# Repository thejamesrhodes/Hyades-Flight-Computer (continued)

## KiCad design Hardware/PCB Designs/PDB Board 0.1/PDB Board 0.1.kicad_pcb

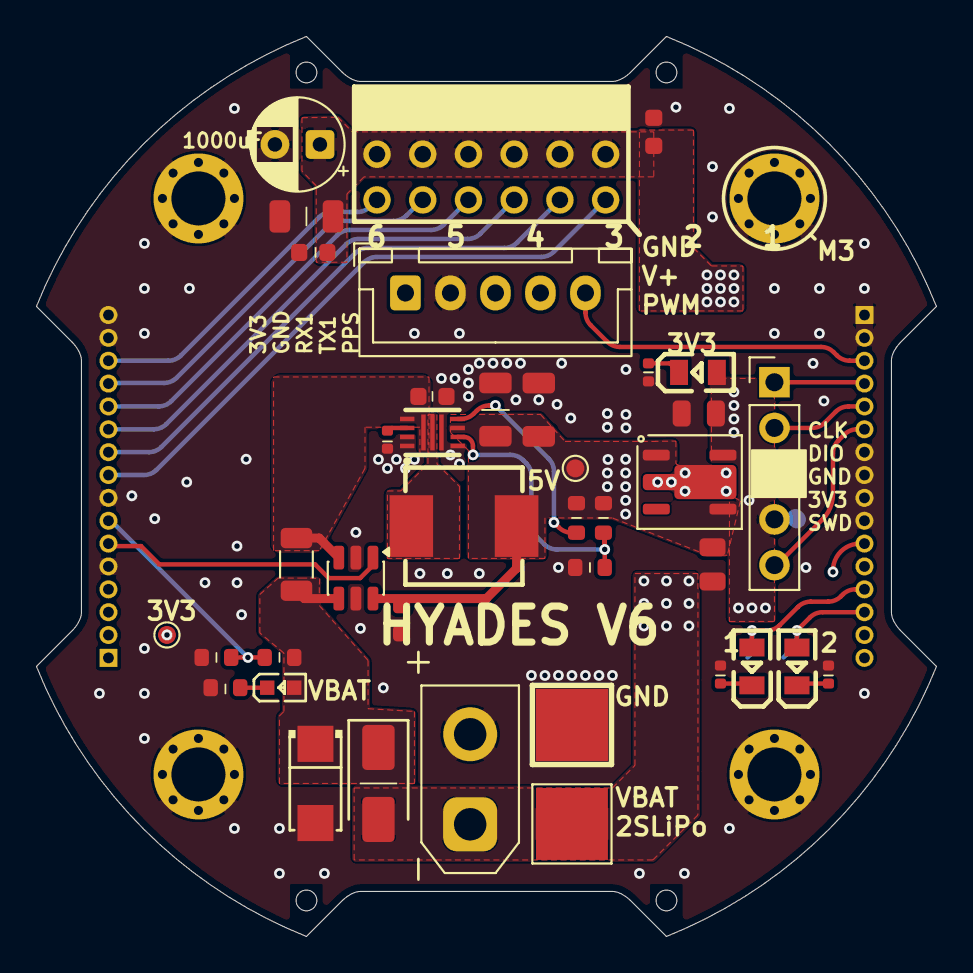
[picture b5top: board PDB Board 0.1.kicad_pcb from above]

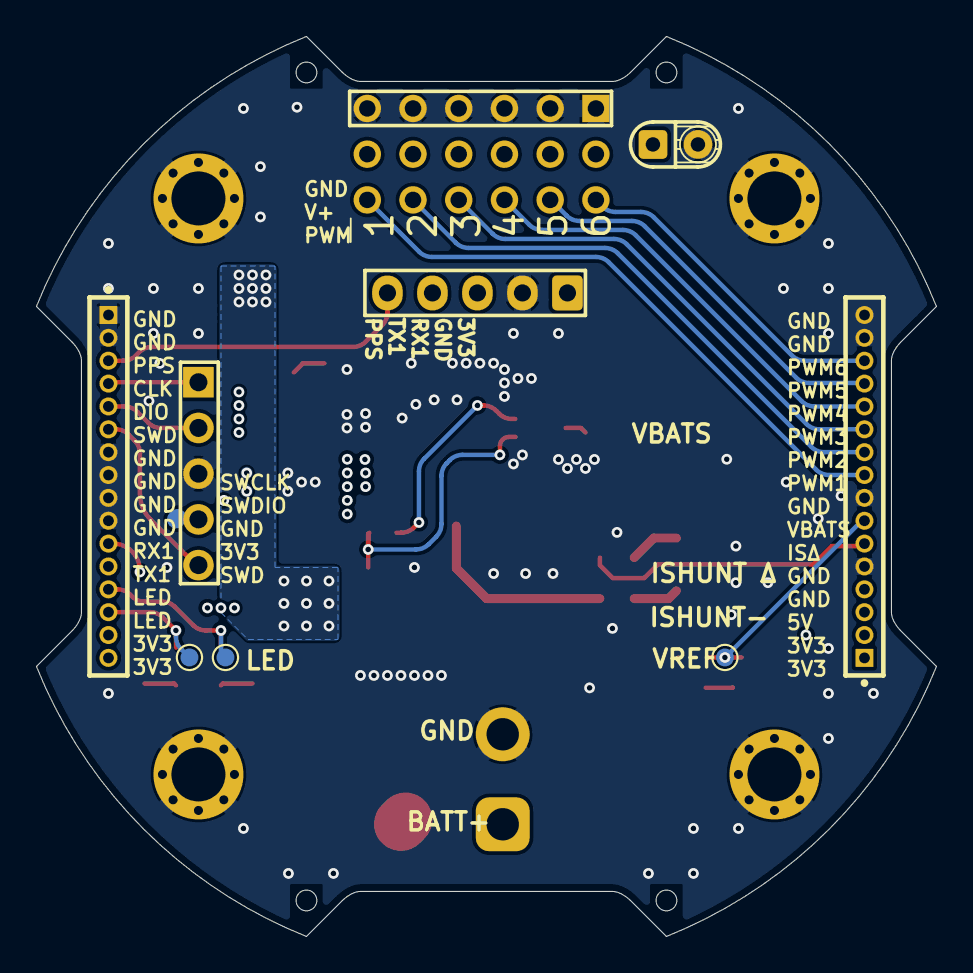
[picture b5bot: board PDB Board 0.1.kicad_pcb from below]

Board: 4 copper layers, 50.0 x 50.0 mm, 52 parts (5 on the bottom side), 30 nets.

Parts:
BT1: Battery; AMASS_XT30UPB-M_1x02_P5.0mm_Vertical
C1, C4, C5: 100nF; C_0603
C6, C7: 10uF; C_1206
C9: 1000uF_16V; CP_Radial_D5.0mm_P2.50mm
C10: 100uF; C_1206
C11, C12: 10uF; C_0805
C18: 10uF; C_0603
C19: 2.2nF; C_0402
D1: SMAJ15A_C908769
D2: SS34; D_SMA
H1, H2, H3, H4: Hole, 3mm
H5, H6, H7, H8: Hole_Tooling_JLCPCB
H9: HX_PZ2_54-3X6P_ZZ
J7: Conn_01x05; JST_XH_B5B-XH-A_1x05_P2.50mm_Vertical
J8: Conn_01x05; PinHeader_1x05_P2.54mm_Vertical
LED1: KT-0603R
LED2, LED4: 17-21SUYC_TR8
LED3: 0805G_Green
R1: 100kΩ; R_0603
R2: 33kΩ; R_0603
R3: 10m_1206_250mW; R_1206_3216Metric
R4: 180kΩ; R_0603
R5: 470Ω; R_0603
R6, R7, R8: 220Ω; R_0402
R15: 62kΩ; R_0603
R16: 10kΩ; R_0603
TP1: BATT-; TestPoint_Pad_4.0x4.0mm
TP2: BATT+; TestPoint_Pad_4.0x4.0mm
TP3, TP4, TP13, TP16, TP17: TestPoint; TestPoint_Pad_D1.0mm
U1: TPS62135RGXR
U2: IHLP2525CZER1R0M01
U3: INA181A1IDBVT; SOT-23-6
U4: AP2115R5A-3.3TRG1; Diodes_SOT-89-5
U6, U7: X1311FV-16-C43D24

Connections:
+3V3: C12.1, J7.1, J8.4, LED2.1 (+), TP4.1 (1_1), U4.5 (OUT), U6.1, U6.2, U7.15, U7.16
+5V: C5.1, C6.1, C7.1, C11.1, R1.2, R15.1, TP3.1 (1_1), U1.6 (VOS), U2.2, U3.6 (V+), U4.1 (EN), U4.4 (IN), U6.3, U6.4
+BATT: BT1.1 (+), C1.1, C4.1, C9.1, C10.1, D2.2, H9.7, H9.8, H9.9, H9.10, H9.11, H9.12, TP2.1 (1_1)
/VDD_BUCK: C18.1, R3.2, U1.1 (VIN), U1.8 (EN), U3.3 (+)
GND: BT1.2 (-), C1.2, C4.2, C5.2, C6.2, C7.2, C9.2, C10.2, C11.2, C12.2, C18.2, C19.2, D1.2, H1.1, H2.1, H3.1, H4.1, H9.1, H9.2, H9.3, H9.4, H9.5, H9.6, J7.2, J8.3, R2.2, R5.1, R6.2, R7.2, R8.2, R16.2, TP1.1 (1_1), U1.3 (GND), U1.4 (FB2), U1.10 (MODE), U1.11 (VSEL), U3.2 (GND), U3.5 (REF), U4.2, U6.5, U6.8, U6.15, U6.16, U7.1, U7.2, U7.7, U7.8, U7.9, U7.10
ISHUNT_DELTA: U3.1 (OUT), U6.6
unnamed: LED1.1 (K), R5.2
unnamed: LED2.2 (-), R6.1
unnamed: LED3.1 (A), TP16.1 (1_1), U7.13
unnamed: LED3.2 (K), R7.1
unnamed: LED4.1 (+), TP17.1 (1_1), U7.14
unnamed: LED4.2 (-), R8.1
unnamed: R15.2, R16.1, U1.5 (FB)
unnamed: R1.1, U1.7 (PG)
unnamed: C19.1, U1.9 (SS/TR)
unnamed: U1.2 (SW), U2.1
PPS: J7.5, U7.3
PWM1: H9.18, U6.9
PWM2: H9.17, U6.10
PWM3: H9.16, U6.11
PWM4: H9.15, U6.12
PWM5: H9.14, U6.13
PWM6: H9.13, U6.14
RX1: J7.3, U7.11
SWCLK: J8.1, U7.4
SWD: J8.5, U7.6
SWDIO: J8.2, U7.5
TX1: J7.4, U7.12
VBAT_SENSE: R2.1, R4.2, TP13.1 (1_1), U6.7
VDD: D1.1, D2.1, LED1.2 (A), R3.1, R4.1, U3.4 (-)

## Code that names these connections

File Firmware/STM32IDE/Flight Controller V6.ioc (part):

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Mcu.Name=STM32H743VITx
Mcu.Package=LQFP100
Mcu.UserName=STM32H743VITx
PA0.GPIOParameters=GPIO_Label
PA0.GPIO_Label=PPS
PA0.Signal=S_TIM2_CH1_ETR
PA11.GPIOParameters=GPIO_Label
PA11.GPIO_Label=USB_D-
PA11.Mode=Device_Only
PA11.Signal=USB_OTG_FS_DM
PA12.GPIOParameters=GPIO_Label
PA12.GPIO_Label=USB_D+
PA12.Mode=Device_Only
PA12.Signal=USB_OTG_FS_DP
PA13\ (JTMS/SWDIO).GPIOParameters=GPIO_Label
PA13\ (JTMS/SWDIO).GPIO_Label=SWDIO
PA13\ (JTMS/SWDIO).Mode=Trace_Asynchronous_SW
PA13\ (JTMS/SWDIO).Signal=DEBUG_JTMS-SWDIO
PA14\ (JTCK/SWCLK).GPIOParameters=GPIO_Label
PA14\ (JTCK/SWCLK).GPIO_Label=SWCLK
PA14\ (JTCK/SWCLK).Mode=Trace_Asynchronous_SW
PA14\ (JTCK/SWCLK).Signal=DEBUG_JTCK-SWCLK
PA6.GPIOParameters=GPIO_Label
PA6.GPIO_Label=VBAT_SENSE
PA6.Signal=ADCx_INP3
PA7.GPIOParameters=GPIO_Label
PA7.GPIO_Label=PWM2
PA7.Signal=S_TIM3_CH2
PA8.GPIOParameters=GPIO_Label
PA8.GPIO_Label=SCL1
PA8.Mode=I2C
PA8.Signal=I2C3_SCL
PA9.GPIOParameters=GPIO_Label
PA9.GPIO_Label=VBUS_SENSE
PA9.Signal=GPIO_Input
PB0.GPIOParameters=GPIO_Label
PB0.GPIO_Label=PWM3
PB0.Signal=S_TIM3_CH3
PB1.GPIOParameters=GPIO_Label
PB1.GPIO_Label=PWM4
PB1.Signal=S_TIM3_CH4
PB12.GPIOParameters=PinState,GPIO_Label
PB12.GPIO_Label=CS2
PB12.PinState=GPIO_PIN_SET
PB12.Signal=GPIO_Output
PB14.GPIOParameters=GPIO_Label
PB14.GPIO_Label=TX2
PB14.Mode=Asynchronous
PB14.Signal=USART1_TX
PB15.GPIOParameters=GPIO_Label
PB15.GPIO_Label=RX2
PB15.Mode=Asynchronous
PB15.Signal=USART1_RX
PB2.GPIOParameters=GPIO_Label
PB2.GPIO_Label=SPI_MOSI2
PB2.Mode=Full_Duplex_Master
PB2.Signal=SPI3_MOSI
PB3\ (JTDO/TRACESWO).GPIOParameters=GPIO_Label
PB3\ (JTDO/TRACESWO).GPIO_Label=SWO
PB3\ (JTDO/TRACESWO).Mode=Trace_Asynchronous_SW
PB3\ (JTDO/TRACESWO).Signal=DEBUG_JTDO-SWO
PB4\ (NJTRST).GPIOParameters=GPIO_Label
PB4\ (NJTRST).GPIO_Label=PWM1
PB4\ (NJTRST).Signal=S_TIM3_CH1
PC10.GPIOParameters=GPIO_Label
PC10.GPIO_Label=SPI_SCK2
PC10.Mode=Full_Duplex_Master
PC10.Signal=SPI3_SCK
PC11.GPIOParameters=GPIO_Label
PC11.GPIO_Label=SPI_MISO2
PC11.Mode=Full_Duplex_Master
PC11.Signal=SPI3_MISO
PC13.GPIOParameters=PinState,GPIO_Label
PC13.GPIO_Label=CS1
PC13.PinState=GPIO_PIN_SET
PC13.Signal=GPIO_Output
PC4.GPIOParameters=GPIO_Label
PC4.GPIO_Label=VSERVO_SENSE
PC4.Signal=ADCx_INP4
PC6.GPIOParameters=GPIO_Label
PC6.GPIO_Label=INT_2
PC6.Signal=GPXTI6
PC7.GPIOParameters=GPIO_Label
PC7.GPIO_Label=INT_1
PC7.Signal=GPXTI7
PC9.GPIOParameters=GPIO_Label
PC9.GPIO_Label=SDA1
PC9.Mode=I2C
PC9.Signal=I2C3_SDA
PD0.GPIOParameters=GPIO_Label
PD0.GPIO_Label=GPIO1
PD0.Signal=GPIO_Output
PD1.GPIOParameters=GPIO_Label
PD1.GPIO_Label=GPIO2
PD1.Signal=GPIO_Output
PD12.GPIOParameters=GPIO_Label
PD12.GPIO_Label=SCL2
PD12.Mode=I2C
PD12.Signal=I2C4_SCL
PD13.GPIOParameters=GPIO_Label
PD13.GPIO_Label=SDA2
PD13.Mode=I2C
PD13.Signal=I2C4_SDA
PD14.GPIOParameters=GPIO_Label
PD14.GPIO_Label=BUZZER
PD14.Signal=S_TIM4_CH3
PD2.GPIOParameters=GPIO_Label
PD2.GPIO_Label=GPIO3
PD2.Signal=GPIO_Output
PD3.GPIOParameters=GPIO_Label
PD3.GPIO_Label=GPIO4
PD3.Signal=GPIO_Output
PD8.GPIOParameters=GPIO_Label
PD8.GPIO_Label=TX1
PD8.Mode=Asynchronous
PD8.Signal=USART3_TX
PD9.GPIOParameters=GPIO_Label
PD9.GPIO_Label=RX1
PD9.Mode=Asynchronous
PD9.Signal=USART3_RX
PE11.GPIOParameters=GPIO_Label
PE11.GPIO_Label=PWM6
PE11.Signal=S_TIM1_CH2
PE2.GPIOParameters=GPIO_Label
PE2.GPIO_Label=SPI_SCK1
PE2.Mode=Full_Duplex_Master
PE2.Signal=SPI4_SCK
PE5.GPIOParameters=GPIO_Label
PE5.GPIO_Label=SPI_MISO1
PE5.Mode=Full_Duplex_Master
PE5.Signal=SPI4_MISO
PE6.GPIOParameters=GPIO_Label
PE6.GPIO_Label=SPI_MOSI1
PE6.Mode=Full_Duplex_Master
PE6.Signal=SPI4_MOSI
PE9.GPIOParameters=GPIO_Label
PE9.GPIO_Label=PWM5
PE9.Signal=S_TIM1_CH1
PH0-OSC_IN\ (PH0).GPIOParameters=GPIO_Label
PH0-OSC_IN\ (PH0).GPIO_Label=HSE_IN
PH0-OSC_IN\ (PH0).Mode=HSE-External-Clock-Source
PH0-OSC_IN\ (PH0).Signal=RCC_OSC_IN
RCC.HSE_VALUE=24000000
RCC.SYSCLKFreq_VALUE=480000000
RCC.SYSCLKSource=RCC_SYSCLKSOURCE_PLLCLK
board=custom

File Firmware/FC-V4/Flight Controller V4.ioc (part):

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Mcu.Name=STM32F411C(C-E)Ux
Mcu.Package=UFQFPN48
Mcu.UserName=STM32F411CEUx
PA0-WKUP.Signal=GPIO_Output
PA1.GPIOParameters=GPIO_Label
PA1.GPIO_Label=LED_2
PA1.Signal=GPIO_Output
PA10.GPIOParameters=GPIO_Label
PA10.GPIO_Label=RX_1
PA10.Mode=Asynchronous
PA10.Signal=USART1_RX
PA11.GPIOParameters=GPIO_Label
PA11.GPIO_Label=USB_D-
PA11.Mode=Device_Only
PA11.Signal=USB_OTG_FS_DM
PA12.GPIOParameters=GPIO_Label
PA12.GPIO_Label=USB_D+
PA12.Mode=Device_Only
PA12.Signal=USB_OTG_FS_DP
PA13.GPIOParameters=GPIO_Label
PA13.GPIO_Label=SWDIO
PA13.Mode=Serial_Wire
PA13.Signal=SYS_JTMS-SWDIO
PA14.GPIOParameters=GPIO_Label
PA14.GPIO_Label=SWCLK
PA14.Mode=Serial_Wire
PA14.Signal=SYS_JTCK-SWCLK
PA15.GPIOParameters=GPIO_Label
PA15.GPIO_Label=TX_1
PA15.Mode=Asynchronous
PA15.Signal=USART1_TX
PA5.GPIOParameters=GPIO_Label
PA5.GPIO_Label=PWM_1
PA5.Signal=S_TIM2_CH1_ETR
PA6.GPIOParameters=GPIO_Label
PA6.GPIO_Label=PWM_2
PA6.Signal=S_TIM3_CH1
PA7.GPIOParameters=GPIO_Label
PA7.GPIO_Label=PWM_3
PA7.Signal=S_TIM3_CH2
PB0.GPIOParameters=GPIO_Label
PB0.GPIO_Label=PWM_4
PB0.Signal=S_TIM3_CH3
PB1.GPIOParameters=GPIO_Label
PB1.GPIO_Label=PWM_5
PB1.Signal=S_TIM3_CH4
PB10.GPIOParameters=GPIO_Label
PB10.GPIO_Label=PWM_6
PB10.Signal=S_TIM2_CH3
PB12.GPIOParameters=GPIO_Label
PB12.GPIO_Label=SPI_SCK
PB12.Mode=Full_Duplex_Master
PB12.Signal=SPI3_SCK
PB3.GPIOParameters=GPIO_Label
PB3.GPIO_Label=SWO
PB3.Signal=SYS_JTDO-SWO
PB4.GPIOParameters=GPIO_Label
PB4.GPIO_Label=MISO
PB4.Mode=Full_Duplex_Master
PB4.Signal=SPI3_MISO
PB5.GPIOParameters=GPIO_Label
PB5.GPIO_Label=MOSI
PB5.Mode=Full_Duplex_Master
PB5.Signal=SPI3_MOSI
PB6.GPIOParameters=GPIO_Label
PB6.GPIO_Label=SCL_1
PB6.Mode=I2C
PB6.Signal=I2C1_SCL
PB7.GPIOParameters=GPIO_Label
PB7.GPIO_Label=SDA_1
PB7.Mode=I2C
PB7.Signal=I2C1_SDA
PH0\ -\ OSC_IN.GPIOParameters=GPIO_Label
PH0\ -\ OSC_IN.GPIO_Label=CLK_IN
PH0\ -\ OSC_IN.Mode=HSE-External-Clock-Source
PH0\ -\ OSC_IN.Signal=RCC_OSC_IN
PH1\ -\ OSC_OUT.GPIOParameters=GPIO_Label
PH1\ -\ OSC_OUT.GPIO_Label=CLK_OUT
PH1\ -\ OSC_OUT.Mode=HSE-External-Clock-Source
PH1\ -\ OSC_OUT.Signal=RCC_OSC_OUT
RCC.HSE_VALUE=25000000
RCC.SYSCLKFreq_VALUE=96000000
RCC.SYSCLKSource=RCC_SYSCLKSOURCE_PLLCLK
board=custom
